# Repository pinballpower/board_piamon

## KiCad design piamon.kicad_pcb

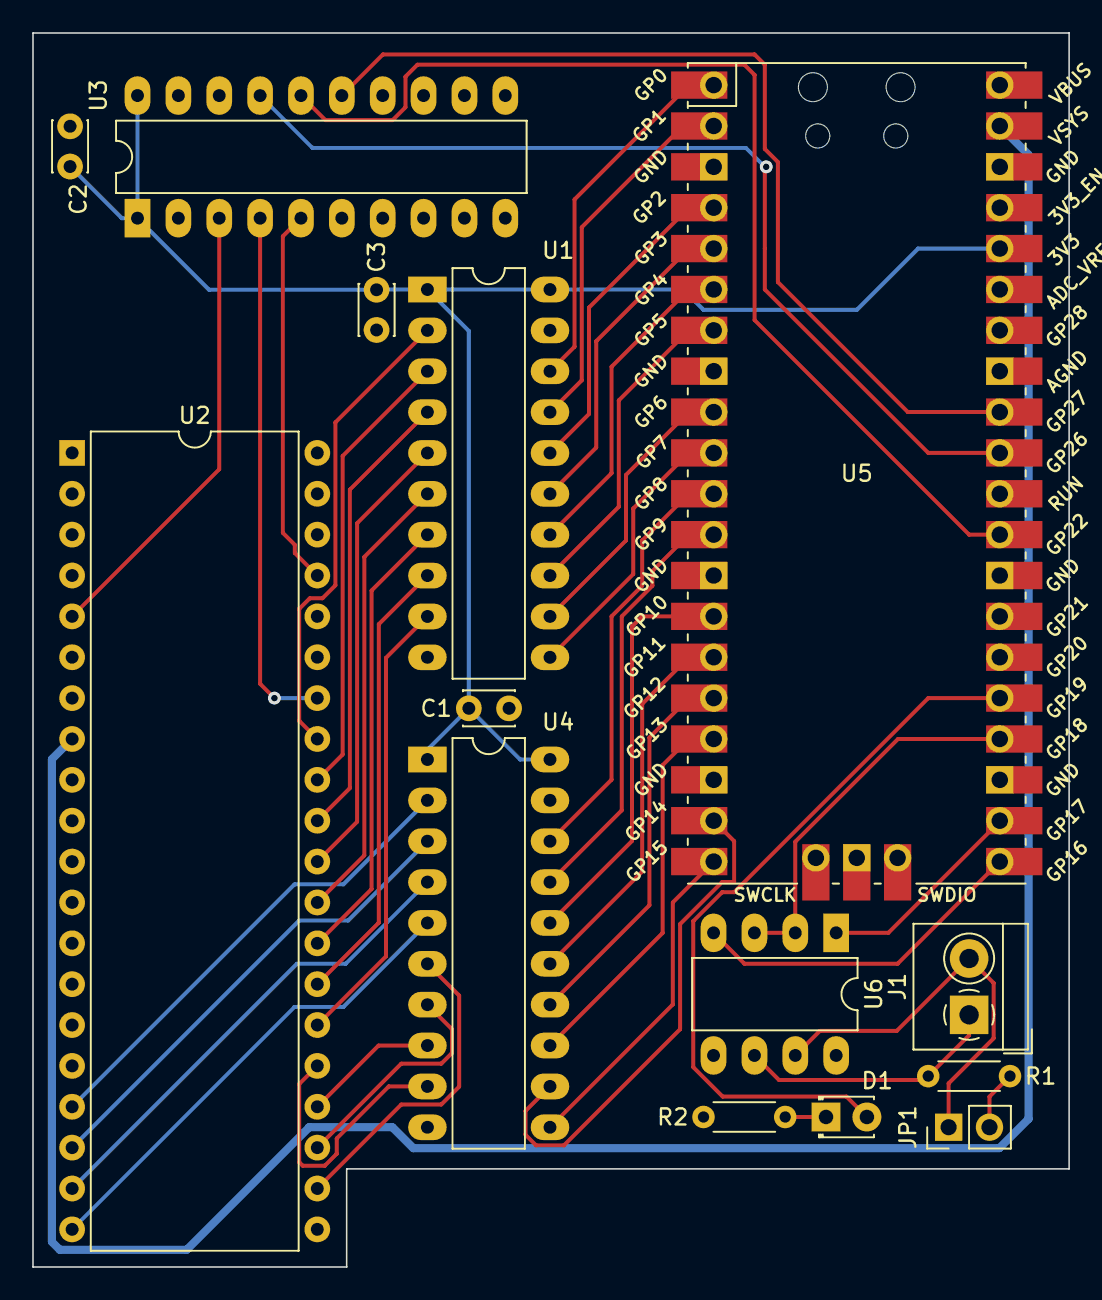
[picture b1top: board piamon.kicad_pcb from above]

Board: 2 copper layers, 64.4 x 76.7 mm, 14 parts (0 on the bottom side), 49 nets.

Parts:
C1, C2, C3: 100n; C_Disc_D3.0mm_W2.0mm_P2.50mm
D1: LED; LED_D1.8mm_W3.3mm_H2.4mm
J1: Screw_Terminal_01x02; TerminalBlock_4Ucon_1x02_P3.50mm_Horizontal
JP1: Jumper; PinHeader_1x02_P2.54mm_Vertical
R1, R2: R; R_Axial_DIN0204_L3.6mm_D1.6mm_P5.08mm_Horizontal
U1, U3, U4: 74HC245; DIP-20_W7.62mm_LongPads
U2: 6808; DIP-40_W15.24mm
U5: Pico; RPi_Pico_SMD_TH
U6: MAX485E; DIP-8_W7.62mm_LongPads

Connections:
+3V3: C1.1, C2.1, C3.1, U1.1 (A->B), U1.20 (VCC), U3.1 (A->B), U3.20 (VCC), U4.1 (A->B), U4.20 (VCC), U5.36 (3V3)
+5V: U2.8 (VCC), U5.39 (VSYS)
/cpu/A8: U4.18 (B0), U5.11 (GPIO8)
/cpu/A9: U4.17 (B1), U5.12 (GPIO9)
/cpu/A10: U4.16 (B2), U5.14 (GPIO10)
/cpu/A11: U4.15 (B3), U5.15 (GPIO11)
/cpu/A12: U4.14 (B4), U5.16 (GPIO12)
/cpu/A13: U4.13 (B5), U5.17 (GPIO13)
/cpu/A14: U4.12 (B6), U5.19 (GPIO14)
/cpu/A15: U4.11 (B7), U5.20 (GPIO15)
/cpu/D0: U1.18 (B0), U5.1 (GPIO0)
/cpu/D1: U1.17 (B1), U5.2 (GPIO1)
/cpu/D2: U1.16 (B2), U5.4 (GPIO2)
/cpu/D3: U1.15 (B3), U5.5 (GPIO3)
/cpu/D4: U1.14 (B4), U5.6 (GPIO4)
/cpu/D5: U1.13 (B5), U5.7 (GPIO5)
/cpu/D6: U1.12 (B6), U5.9 (GPIO6)
/cpu/D7: U1.11 (B7), U5.10 (GPIO7)
/cpu/E: U3.15 (B3), U5.32 (GPIO27_ADC1)
/cpu/R/W: U3.16 (B2), U5.29 (GPIO22)
/cpu/VMA: U3.17 (B1), U5.31 (GPIO26_ADC0)
GND: C1.2, C2.2, C3.2, R2.2, U1.10 (GND), U1.19 (CE), U2.1 (VSS), U2.21 (VSS), U3.10 (GND), U3.19 (CE), U4.10 (GND), U4.19 (CE), U5.3 (GND), U5.8 (GND), U5.13 (GND), U5.18 (GND), U5.23 (GND), U5.28 (GND), U5.33 (AGND), U5.38 (GND)
unnamed: D1.1 (K), R2.1
unnamed: D1.2 (A), U5.25 (GPIO19)
unnamed: J1.1, R1.1, U6.6 (A)
unnamed: J1.2, JP1.1, U6.7 (B)
unnamed: JP1.2, R1.2
unnamed: U1.2 (A0), U2.33 (D0)
unnamed: U1.3 (A1), U2.32 (D1)
unnamed: U1.4 (A2), U2.31 (D2)
unnamed: U1.5 (A3), U2.30 (D3)
unnamed: U1.6 (A4), U2.29 (D4)
unnamed: U1.7 (A5), U2.28 (D5)
unnamed: U1.8 (A6), U2.27 (D6)
unnamed: U1.9 (A7), U2.26 (D7)
unnamed: U2.5 (VMA), U3.3 (A1)
unnamed: U2.17 (A8), U4.2 (A0)
unnamed: U2.18 (A9), U4.3 (A1)
unnamed: U2.19 (A10), U4.4 (A2)
unnamed: U2.20 (A11), U4.5 (A3)
unnamed: U2.22 (A12), U4.6 (A4)
unnamed: U2.23 (A13), U4.7 (A5)
unnamed: U2.24 (A14), U4.8 (A6)
unnamed: U2.25 (A15), U4.9 (A7)
unnamed: U2.34 (R/~W), U3.4 (A2)
unnamed: U2.37 (Phi2), U3.5 (A3)
unnamed: U5.21 (GPIO16), U6.4 (DI)
unnamed: U5.22 (GPIO17), U6.1 (RO)
unnamed: U5.24 (GPIO18), U6.2 (~RE), U6.3 (DE)

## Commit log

2021-09-13 Initial checkin
2021-09-13 Added MIT license
2021-11-01 Update LICENSE
